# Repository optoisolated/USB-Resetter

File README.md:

# USB Resetter

The USB Resetter allows for using a 5V power source such as a GPIO Pin on a Raspberry Pi or Arduino to enable/disable a USB A connection. This was designed to facilitate allowing my Raspberry Pi to Reset my Fine Offset Weather Station which suffers from USB Lockup, and the only recourse is to forcibly power-cycle the device. 

This device uses a Male and Female USB-A connection to allow for simple installation, and then a 2 PIN GPIO-Compatible input for the reset. The circuit is normally open, so requires power to enable the USB. The device only switches the VBUS Pin on the USB device, so the data pins are not hindered in any way by active circuitry; which may reduce throughput.

The Power Switching circuit uses an optically isolated Solid State Relay to minimise power loss and ensure a clean power transition. The on/off pins directly connect to the LED side of the Optocoupler and are not driven in any way by the USB power line. This ensures no power loss due to the optoisolator LED and also ensures no shared ground between the the USB line and the device performing the switching. 

The ASSR-1218 SSR has been assumed to be run between 3.3v and 5v and has as an in-series resistor to accomodate that. The line can be driven with a higher voltage but will need an appropriate voltage divider and circuit protection. The SSR will draw between 2mA and 20mA in normal operation. The on/off pins are not latched, so need to driven to remain on.

The Bypass switch is driven by the VBUS line and does not need any external power connected in order to work. 

Note that with the Bypass switch in the on position, the On/Off pins will have no effect.

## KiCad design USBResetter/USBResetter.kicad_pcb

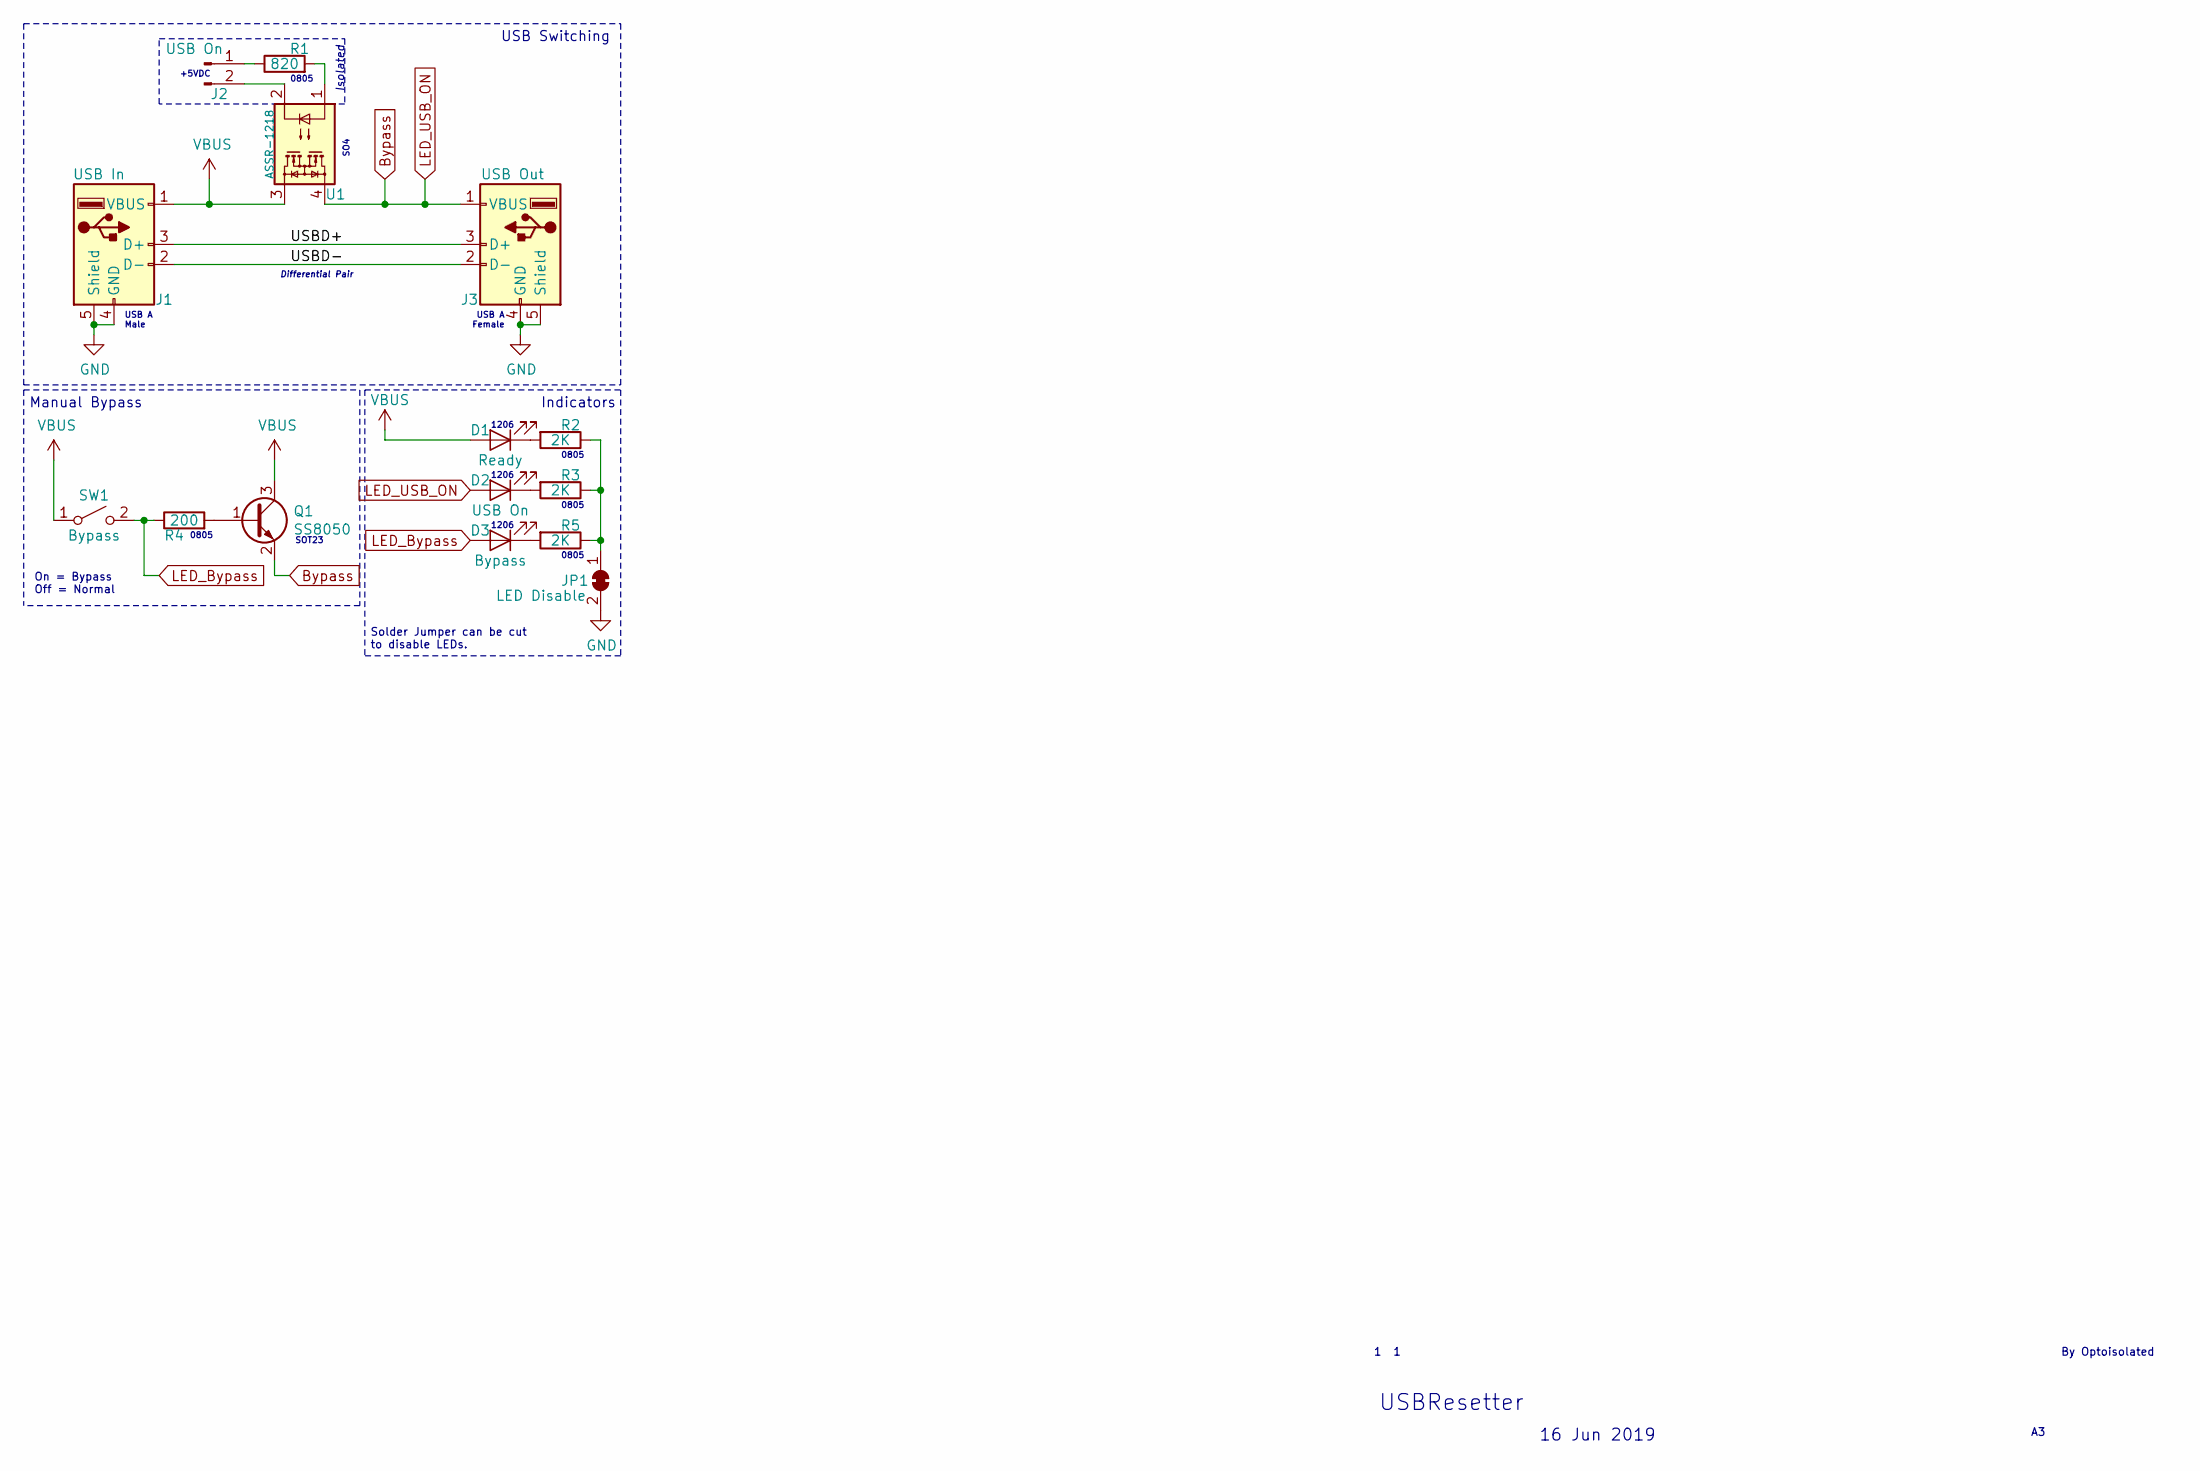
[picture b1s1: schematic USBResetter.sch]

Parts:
D1: Ready; LED_1206
D2: USB On; LED_1206
D3: Bypass; LED_1206
J1: USB In; USB_A
J2: USB On; Pin_Header_Straight_1x02_Pitch2.54mm
J3: USB Out; USB_A
JP1: LED Disable; SolderJumper-2_P1.3mm_Bridged_Pad1.0x1.5mm
Q1: SS8050; SOT-23
R1: 820; R_0805
R2, R3, R5: 2K; R_0805
R4: 200; R_0805
SW1: Bypass; SW_SPST_EVPBF
U1: ASSR-1218; SO-4_4.4x4.3mm_Pitch2.54mm

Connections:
/USBD+: J1.3 (D+), J3.3 (D+)
/USBD-: J1.2 (D-), J3.2 (D-)
Bypass: D2.2 (A), J3.1 (VBUS), Q1.2 (E), U1.4
GND: J1.4 (GND), J1.5 (Shield), J3.4 (GND), J3.5 (Shield), JP1.2 (B)
LED_Bypass: D3.2 (A), R4.1, SW1.2 (B)
unnamed: D1.1 (K), R2.2
unnamed: D2.1 (K), R3.2
unnamed: D3.1 (K), R5.2
unnamed: J2.1, R1.1
unnamed: J2.2, U1.2
unnamed: JP1.1 (A), R2.1, R3.1, R5.1
unnamed: Q1.1 (B), R4.2
unnamed: R1.2, U1.1
VBUS: D1.2 (A), J1.1 (VBUS), Q1.3 (C), SW1.1 (A), U1.3

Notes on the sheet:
+5VDC
USB Switching
Manual Bypass
Indicators
Isolated
Solder Jumper can be cut to disable LEDs.
USBResetter
16 Jun 2019
1 1
By Optoisolated
On = Bypass Off = Normal
Differential Pair
SOT23
1206
USB A Male
USB A Female
SO4
0805

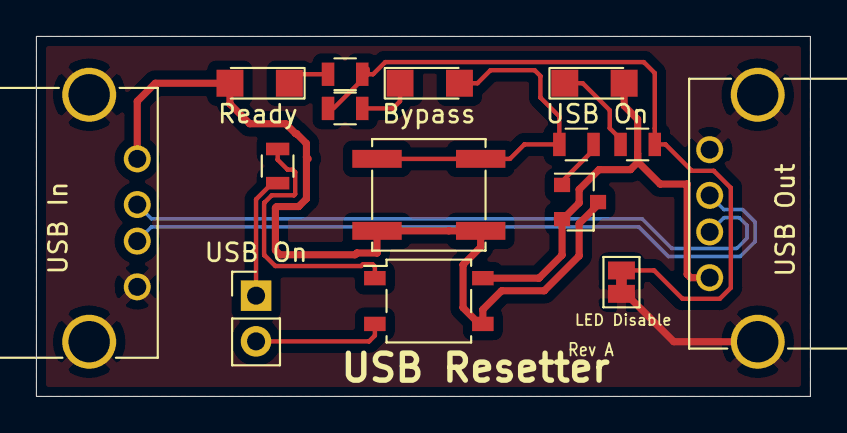
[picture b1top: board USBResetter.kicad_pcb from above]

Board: 2 copper layers, 43.0 x 20.0 mm, 15 parts (0 on the bottom side), 14 nets.

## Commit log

2019-06-14 Layout Formatting
    General layout tidy up.
2019-06-14 PCB Layout, Parts Assignment
2019-06-14 Fixed issues with components and layout
    Replaced Footprint for NPN Transistor to match the Pinout of the Part. Recreated the Data lines using Differential Pair to ensure optimal USB Data speed and minimal interference.
2019-06-14 Generated Gerber Files for Fabrication
2019-06-14 Rev A (#1)
    * Update README.md
    * Update README.md
    * Layout Formatting
    General layout tidy up.
    * PCB Layout, Parts Assignment
    * Fixed issues with components and layout
2019-06-14 Dev (#2)
    * Layout Formatting
    General layout tidy up.
    * PCB Layout, Parts Assignment
    * Fixed issues with components and layout
    Replaced Footprint for NPN Transistor to match the Pinout of the Part. Recreated the Data lines using Differential Pair to ensure optimal USB Data speed and minimal interference.
    * Generated Gerber Files for Fabrication
2019-06-14 Update LICENSE
2019-06-15 Fixed Bypass Transistor issue
    Removed current limiting resistor and connection to ground for the Bypass Transistor, to allow it to work as intended.
2019-06-15 Recreated Rev A Gerbers with Fixes
    Removed CL Resistor on Bypass circuit; Fixed Transister Grounding issue.
2019-06-15 Rev A - With Fixed Bypass
2019-06-15 Removed Gerbers
2019-06-15 Fixed board dimensions issue
    Found one edge was short by 0.2mm.
2019-06-15 Fixed board dimensions issue (#5)
    Found one edge was short by 0.2mm.
2019-06-15 Fixed Board Dimension issue
    Board outline wasn't rendering correctly. Recreated the Edge Cuts layer
2019-06-15 Board Dimension issue resolved. (#6)
    Found one edge was short by 0.2mm.
    * Fixed Board Dimension issue
    * Board outline wasn't rendering correctly. Recreated the Edge Cuts layer
2019-06-16 Bypass LED, Button Centered
    * Added Bypass LED Indicator LED.
    * Moved the Bypass button to center of the board.
    * Simpliflied the ground plane.
    * Properly annotated schematic
2019-06-16 Last Revision A update. (#7)
    Fixed board dimensions issue
    * Found one edge was short by 0.2mm.
    * Fixed Board Dimension issue
    * Board outline wasn't rendering correctly. Recreated the Edge Cuts layer
    Bypass LED, Button Centered
    * Added Bypass LED Indicator LED.
2019-06-16 Layout Update
2019-06-16 Timing Update (#8)
    Fixed board dimensions issue
    * Found one edge was short by 0.2mm.
    Board outline wasn't rendering correctly. Recreated the Edge Cuts layer
    * Bypass LED, Button Centered
    * Added Bypass LED Indicator LED.
    * Moved the Bypass button to center of the board.
2020-01-14 Added 3D Render of PCB
